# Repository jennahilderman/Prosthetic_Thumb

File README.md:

# Prothetic_Thumb
Schematics and code for a custom prosthetic thumb.

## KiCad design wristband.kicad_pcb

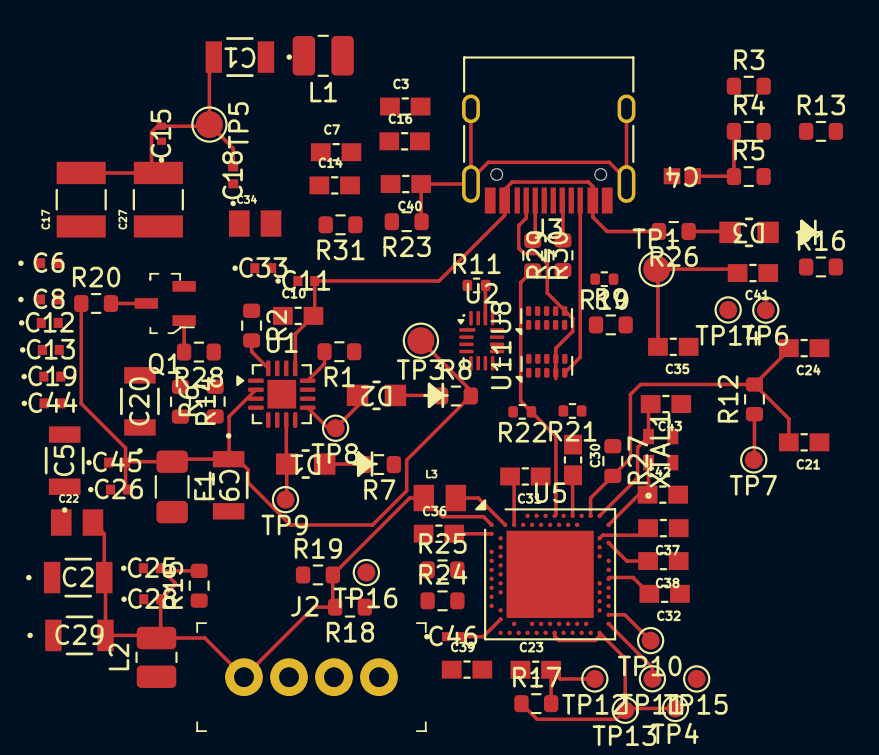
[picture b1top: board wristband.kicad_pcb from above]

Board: 2 copper layers, 108 parts (0 on the bottom side), 50 nets.

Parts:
C1, C2, C5, C9, C20, C29: 22uF 10V X7R 1206; CAP_CC1206_YAG-L
C3, C16, C21, C23, C24, C30, C31, C32, C35, C36, C37, C38, C39, C41: 1uF 10V X7R 0603; CAPC1608X90
C4: 6.8nF 50V C0G/NP0 0603; CAPC17795_95N_KEM-L
C6, C8, C12, C13, C18, C19, C25, C26, C28, C33, C44: 0.1uF 25V X7R 0402; CAP_0402_N_WAL
C7: 6.2n; CAPC1608X90
C10, C14: 10uF 10V X7R 0603; CAPC1608X90
C11, C45: 0.1 uF 10 V X7R 0402; CAP_0402_N_WAL
C15, C46: 0.1 uF 25 V X7R 0402; CAP_0402_N_WAL-L
C17, C27: 47uF 10V X7R 1210; CAPC3225X280N
C22, C34: 4.7uF 25V X7R 0805; CAPC2012X150N
C40: 1nF 10V X7R 0603; CAPC1608X90
C42, C43: 12pF 50V C0G/NPO 0603; CAPC1608X90
D1: LED_BLUE; LED_LTST-C170GKT_LTO
D2: LED_YELLOW; LED_LTST-C170GKT_LTO
D3: LED_GREEN; LED_LTST-C170GKT_LTO
F1: 1.5; Fuse_1206_3216Metric
J2: B4B-XH-A_LF__SN_; PinHeader_1x4_P2.5mm_Drill1.1mm
J3: USB_C_Receptacle; USB_C_Receptacle_HRO_TYPE-C-31-M-12
L1: 3u; L_1008_2520Metric
L2: 2.2u; L_1008_2520Metric
L3: 10µH Isat ≥ 150 mA 0805; INDC2012X145N
Q1: 2N7002; SOT-23-3
R1: 1.1k; R_0603_1608Metric
R2, R7, R8, R26: 1k; R_0603_1608Metric
R3, R4, R6, R14, R15, R17, R20: 100k; R_0603_1608Metric
R5: 27k; R_0603_1608Metric
R9: 5.1k; R_0603_1608Metric
R10: 5.1k; R_0402_1005Metric
R11: 100k; R_0402_1005Metric
R12, R27: 10k; R_0603_1608Metric
R13: 732k; R_0603_1608Metric
R16: 47k; R_0603_1608Metric
R18, R19, R31: 4.7k; R_0603_1608Metric
R21, R22: 27; R_0402_1005Metric
R23: 1M; R_0603_1608Metric
R24, R25, R29, R30: 27; R_0603_1608Metric
R28: 100; R_0603_1608Metric
TP1: TP_VBUS5V; TestPoint_Pad_D1.5mm
TP3: TP_BATT; TestPoint_Pad_D1.5mm
TP4: TP_V3V3; TestPoint_Pad_D1.0mm
TP5: TP_VMOTOR; TestPoint_Pad_D1.5mm
TP6: TP_GND_2; TestPoint_Pad_D1.0mm
TP7: TP_NFAULT; TestPoint_Pad_D1.0mm
TP8: TP_CHG; TestPoint_Pad_D1.0mm
TP9: TP_PG; TestPoint_Pad_D1.0mm
TP10: TP_SWCLK; TestPoint_Pad_D1.0mm
TP11: TP_SWDIO; TestPoint_Pad_D1.0mm
TP12: TP_RESET; TestPoint_Pad_D1.0mm
TP13: TP_VTREF; TestPoint_Pad_D1.0mm
TP14: TP_GND; TestPoint_Pad_D1.0mm
TP15: TP_U6_SCL; TestPoint_Pad_D1.0mm
TP16: TP_U6_SDA; TestPoint_Pad_D1.0mm
U1: BQ24075RGT; VQFN-16-1EP_3x3mm_P0.5mm_EP1.6x1.6mm
U2: TS3USBCA410; UQFN-16_1.8x2.6mm_P0.4mm
U5: nRF52840; Nordic_AQFN-73-1EP_7x7mm_P0.5mm
U8, U11: TPD4E05U06DQA; USON-10_2.5x1.0mm_P0.5mm
XTAL1: NX2016SA-32M-EXS00A-CS06465; NX2016SA_NDK

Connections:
+BATT: C9.1, C26.2, C45.2, F1.1, R8.2, R20.1, TP3.1, U1.2 (BAT), U1.3 (BAT)
/MCU_GPIO: R6.2, R14.1, R28.1, U1.4 (~CE)
/SCL2_P011: J2.2, R19.1, TP15.1, U5.T2 (TRACEDATA2/P0.11)
/SDA2_P012: J2.3, R18.1, TP16.1, U5.U1 (TRACEDATA1/P0.12)
/TP6_SBU1: U2.11 (SBU1), U11.1 (D1+)
/TP6_SBU2: U2.10 (SBU2), U11.2 (D1-)
/U5_P031: R27.1, U5.A8 (AIN7/P0.31)
/U10_VDD: C33.2, C34.2, R31.2
/UART_RX_P008: R24.2, U5.N1 (P0.08)
/UART_TX_P006: R25.2, U5.L1 (P0.06)
/USB_CC1: J3.A5 (CC1), R10.2, U8.4 (D2+)
/USB_CC2: J3.B5 (CC2), R9.1, U8.5 (D2-)
/USB_DM: R21.1, R29.1, U5.B15 (P1.14), U8.2 (D1-)
/USB_DP: R22.1, R30.2, U5.A14 (P1.15), U8.1 (D1+)
/USB_SBU1: J3.A8 (SBU1), U11.4 (D2+)
/USB_SBU2: J3.B8 (SBU2), U11.5 (D2-)
/V3V3: C2.2, C21.2, C22.2, C24.2, C25.2, C28.2, C29.2, J2.1, L2.2, L3.1, R12.2, R15.2, R17.1, R18.2, R19.2, R27.2, TP4.1, TP13.1, U5.A22 (VDD), U5.AD14 (VDD), U5.AD23 (VDD), U5.B1 (VDD), U5.W1 (VDD)
/VBUS5V: C10.2, C11.2, C35.2, C41.2, J3.A4 (VBUS), J3.A9 (VBUS), J3.B4 (VBUS), J3.B9 (VBUS), R26.2, TP1.1, U1.13 (IN)
/VMOTOR: C1.2, C15.2, C17.2, C18.2, C27.2, TP5.1
GND: C4.2, C5.1, C5.2, C6.1, C6.2, C7.2, C8.1, C8.2, C9.2, C10.1, C11.1, C12.1, C12.2, C13.1, C13.2, C14.1, C14.2, C17.1, C18.1, C19.1, C19.2, C20.1, C20.2, C21.1, C22.1, C23.1, C24.1, C25.1, C26.1, C27.1, C28.1, C29.1, C30.1, C31.1, C32.1, C33.1, C34.1, C35.1, C36.1, C37.1, C38.1, C39.1, C40.2, C41.1, C42.2, C43.1, C44.1, C44.2, C45.1, C46.1, D3.1 (K), F1.2, J2.4, J3.A1 (GND), J3.A12 (GND), J3.B1 (GND), J3.B12 (GND), Q1.2 (S), R1.1, R2.1, R3.1, R4.2, R5.2, R6.1, R7.1, R9.2, R10.1, R11.1, R13.2, R16.1, R23.2, TP6.1, TP14.1, U1.5 (EN2), U1.6 (EN1), U1.8 (VSS), U1.10 (OUT), U1.11 (OUT), U1.14 (TMR), U1.15 (SYSOFF), U1.17 (VSS), U2.1 (VCC), U2.2 (MIC_GND1/Ln1), U2.3 (MIC_GND2/Ln2), U2.4 (~OE), U2.9 (GND), U2.12 (I2C_EN), U2.15 (LnAn), U5.B7 (VSS), U5.EP (VSS), U8.3 (GND), U8.8 (GND), U11.3 (GND), U11.8 (GND), XTAL1.2, XTAL1.3
unnamed: D1.2 (A), TP9.1, U1.7 (~PGOOD)
unnamed: D1.1 (K), R7.2
unnamed: D2.2 (A), TP8.1, U1.9 (~CHG)
unnamed: D2.1 (K), R8.1
unnamed: D3.2 (A), R26.1
unnamed: J3.A6 (D+), J3.B6 (D+), R30.1
unnamed: J3.A7 (D-), J3.B7 (D-), R29.2
unnamed: C40.1, J3.S1 (SHIELD), R23.1
unnamed: C4.1, R4.1, R5.1
unnamed: C1.1, L1.2
unnamed: Q1.3 (D), R20.2
unnamed: Q1.1 (G), R28.2
unnamed: R1.2, U1.12 (ILIM)
unnamed: R2.2, U1.16 (ISET)
unnamed: R11.2, U2.14 (FLIP)
unnamed: R12.1, TP7.1
unnamed: L3.2, U5.B3 (DCC)
unnamed: C46.2, U5.AB2 (DCCH)
unnamed: C36.2, U5.C1 (DEC1)
unnamed: C30.2, U5.A18 (DEC2)
unnamed: C37.2, U5.D23 (DEC3)
unnamed: C31.2, U5.B5 (DEC4)
unnamed: C32.2, U5.N24 (DEC5)
unnamed: C38.2, U5.E24 (DEC6)
unnamed: C39.2, U5.AC5 (DECUSB)
unnamed: C23.2, R17.2, TP12.1, U5.AC13 (P0.18/~RESET)
unnamed: TP10.1, U5.AA24 (SWDCLK)
unnamed: TP11.1, U5.AC24 (SWDIO)
unnamed: C42.1, U5.B24 (XC1), XTAL1.1
unnamed: C43.2, U5.A23 (XC2), XTAL1.4
